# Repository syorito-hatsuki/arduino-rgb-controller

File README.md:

# RGB-IR-Controller
IR controller for 12V RGB led strip based on Arduino Nano

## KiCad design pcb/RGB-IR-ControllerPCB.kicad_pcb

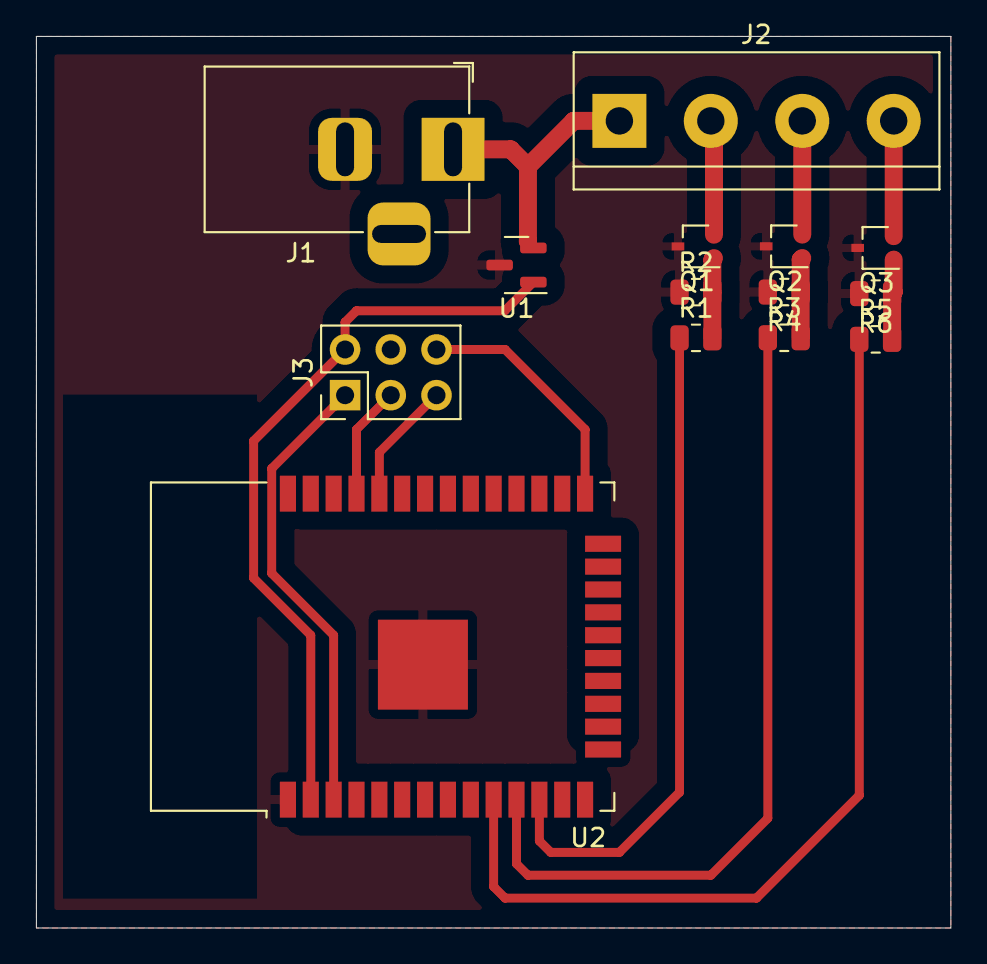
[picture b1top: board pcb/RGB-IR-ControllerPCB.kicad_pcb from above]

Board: 2 copper layers, 50.8 x 49.5 mm, 14 parts (0 on the bottom side), 16 nets.

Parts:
J1: Barrel_Jack; BarrelJack_Horizontal
J2: RGB_WIRES; TerminalBlock_bornier-4_P5.08mm
J3: UART; PinHeader_2x03_P2.54mm_Vertical
Q1, Q2, Q3: IRF540N; SOT-323_SC-70
R1, R3, R5: 100; R_0805_2012Metric
R2, R4, R6: 10K; R_0805_2012Metric
U1: LM3480-3.3; SOT-23
U2: ESP32-WROOM-32D; ESP32-WROOM-32

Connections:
+3.3V: J3.2, U1.1 (VO), U2.2 (VDD)
+12V: J1.1, J2.1, U1.2 (VI)
BLUE_PIN: R5.1, U2.10 (IO25)
BLUE_WIRE: J2.4, Q3.2 (D)
ESP_BOOT: J3.6, U2.25 (IO0)
ESP_EN: J3.1, U2.3 (EN)
ESP_RXD: J3.5, U2.34 (RXD0/IO3)
ESP_TXD: J3.3, U2.35 (TXD0/IO1)
GND: J1.2, J3.4, Q1.3 (S), Q2.3 (S), Q3.3 (S), R2.1, R4.2, R6.2, U1.3 (GND), U2.1 (GND), U2.15 (GND), U2.38 (GND), U2.39 (GND)
GREEN_PIN: R1.1, U2.12 (IO27)
GREEN_WIRE: J2.2, Q1.2 (D)
unnamed: Q2.1 (G), R3.2, R4.1
unnamed: Q1.1 (G), R1.2, R2.2
unnamed: Q3.1 (G), R5.2, R6.1
RED_PIN: R3.1, U2.11 (IO26)
RED_WIRE: J2.3, Q2.2 (D)

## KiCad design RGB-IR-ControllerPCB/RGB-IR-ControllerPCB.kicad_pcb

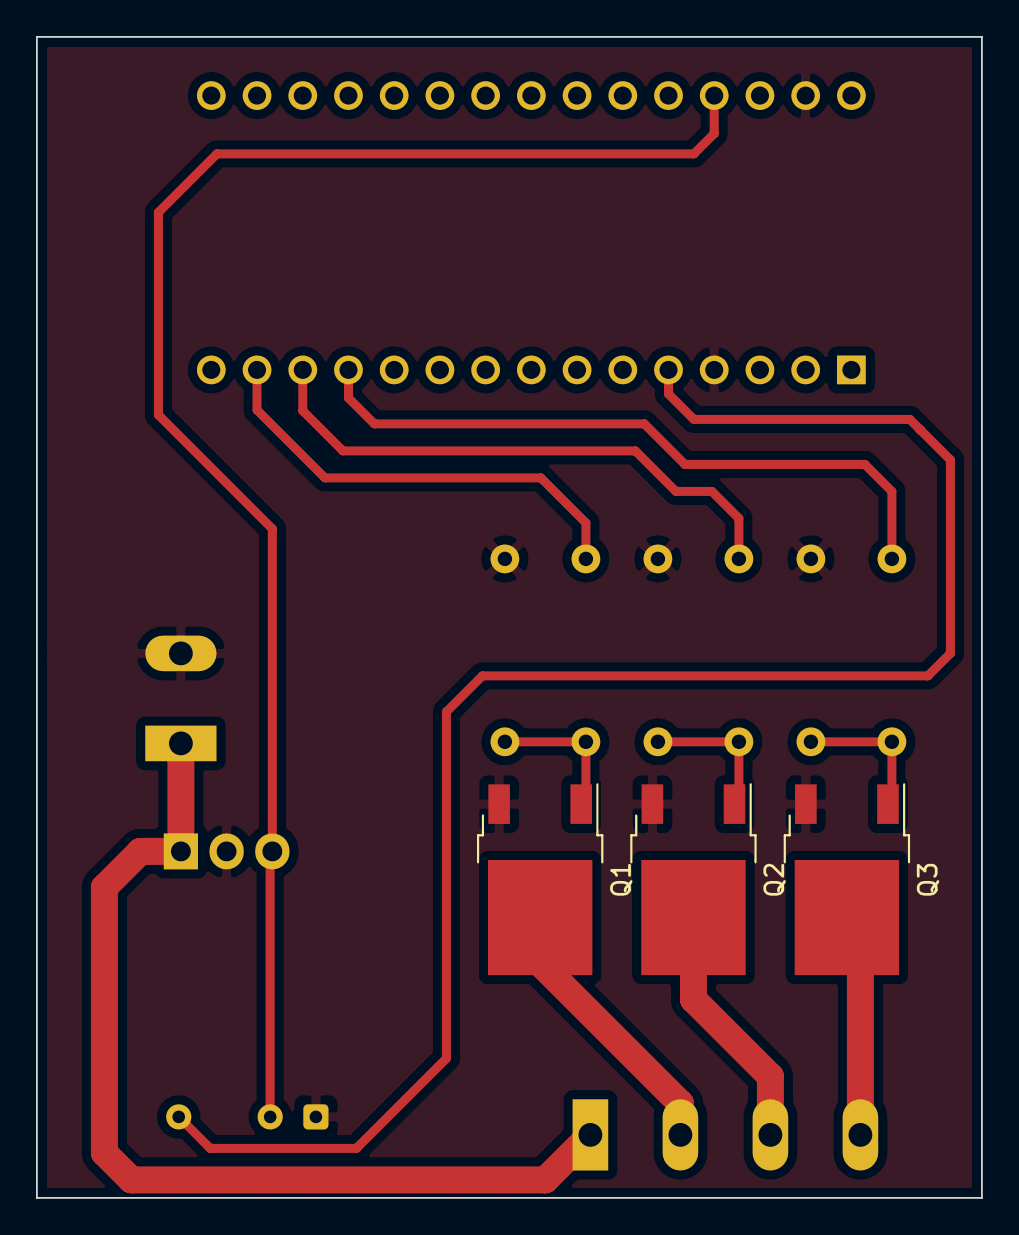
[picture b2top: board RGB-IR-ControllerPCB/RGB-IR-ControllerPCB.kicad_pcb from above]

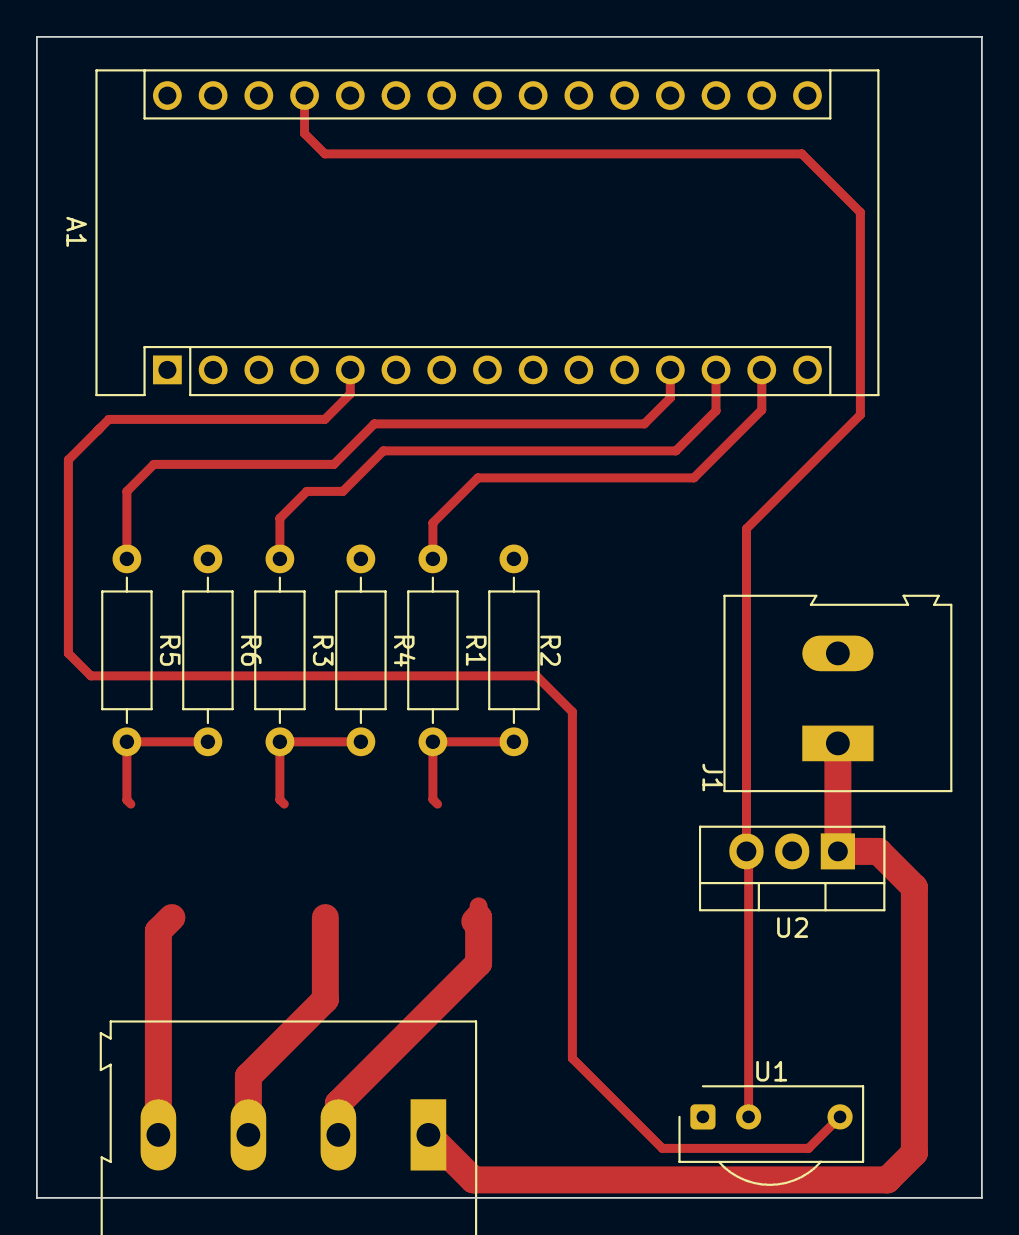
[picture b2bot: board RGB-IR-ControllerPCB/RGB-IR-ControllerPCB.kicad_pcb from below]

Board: 2 copper layers, 52.5 x 64.5 mm, 14 parts (11 on the bottom side), 13 nets.

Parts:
A1: Arduino_Nano_v3.x; Arduino_Nano
J1: Screw_Terminal_01x02; TerminalBlock_Altech_AK300-2_P5.00mm
J2: Screw_Terminal_01x04; TerminalBlock_Altech_AK300-4_P5.00mm
Q1, Q2, Q3: IRF540N; TO-252-2
R1, R3, R5: 100; R_Axial_DIN0207_L6.3mm_D2.5mm_P10.16mm_Horizontal
R2, R4, R6: 10K; R_Axial_DIN0207_L6.3mm_D2.5mm_P10.16mm_Horizontal
U1: TSOP17xx; Vishay_CAST-3Pin
U2: L7805; TO-220-3_Vertical

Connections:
+5V: A1.27, U1.2, U2.3
+12V: J1.1, J2.1, U2.1
BLUE_PIN: A1.12, R5.1
GND: A1.4, A1.29, J1.2, Q1.3, Q2.3, Q3.3, R2.1, R4.1, R6.1, U1.1, U2.2
GREEN_PIN: A1.14, R1.1
IR_DATA_OUT: A1.5, U1.3
unnamed: J2.2, Q1.2
unnamed: J2.3, Q2.2
unnamed: J2.4, Q3.2
unnamed: Q1.1, R1.2, R2.2
unnamed: Q2.1, R3.2, R4.2
unnamed: Q3.1, R5.2, R6.2
RED_PIN: A1.13, R3.1

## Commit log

2021-04-03 Added doned PCB and Schematic for RGB Controller
2021-04-05 Inited code part
2021-04-08 Updated PCB and clear deprecate code
2021-04-08 Created IR library and started RGB Library
2021-04-12 Refactored PCB
2021-04-15 updated pcb smd resistors to tht
2021-04-19 Added 5V Voltage Regulator
2021-04-19 Optimized traces
2021-04-19 Moved IR to attachInterrupt
2021-04-23 Updated libs
2021-04-23 added workspace
2021-04-23 some updates
2021-04-23 null exception fix
2021-04-23 blank rgb bugfix
2021-04-23 tests
2021-04-23 message
2021-04-23 codestyle & bugfix
2021-04-23 Refactor
2021-04-23 Added all effects and fixed speed
2021-04-24 Fixed some effects
2022-09-28 Renamed folders
2022-09-29 PCB prototype without GND connection
